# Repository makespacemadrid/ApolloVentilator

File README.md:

# ApolloVentilator

Information: Checkout our [wiki](https://github.com/makespacemadrid/ApolloVentilator/wiki)

### Schematic

### Prototype 1 @ MakeSpace Madrid

### Prototype 2 @ Miguel's Workshop

## Getting started

### Linux

```
$ apt-get install libcairo2-dev libgirepository1.0-dev python3-cairo-dev
```

### Mac

```
$ brew install pygobject3 gtk+3 libnotify
```

### App (Python 3)

From ```./gui```

Install system dependencies (Debian-based):

```
$ pip install -r requirements.txt
$ ./main.py
```

## Requirements:
2 ventilators mode
* Pressure Regulated Volume Controlled (PCV): set pressure delivered during period of inspiration. The voume measured is shown as data on display. 
* Volume Regulated Pressure controlled (VCV): The tidal volume is set and it adapts the pressure to the lowest. Here the important data are: tidal volume, upper alarm and lower current volume. Useful parameters: tidal volume, respiratory rate. There is a limit pressure and during inspiration period.

If patient stops breathing, there is a failsafe that set to mandatory breathing when it's detected.

During inspiration:

* Inspiration pressure: The plateau pressure is adjusted to volume hard limit (32 cmH2O by default, and could increate to 70cmH2O)
* Peak pressure: 2cmH2O greater than plateau.
* VCV pressure limit (15-40cm2 with increments of 5)
* Failsafe valve that opens always at 80cmH20 (or lower)

* PEEP: 5-10 with increments of 5. The circuit must be pressured.
* IE ratio: 1:1, 1:2, 1:3
* Respiratory rate: 10-30 bpm with increments of 2.
* Tidal volume: 40ml +-10, 350 +-50, 250-600 +-50,up to 8000. 
* Weight body and volume calculated based on 6ml/kg.

## Alarms

* Gas failure
* Electricity failure
* Machine switched off
* Inspiration pressure exceeded
* Inspiration pressure not achieved
* PEEP pressure not achieved
* Tidal volume not achieved
* Tidal volume exceeded
* Resistance: peak pressure - plateau pressure > 2cmH2O
* Compliance
* Volume Leakage

## Monitoring
### Settings
* Tidal volume
* Frequency
* PEEP
* FI02
* Ventilation Mode

### Current status
* Tidal volume
* Breathing rate
* PEEP
* Plateau pressure
* FI02

The normal healthy O2 consuption is 250mL/min, and could be increased until, for example 500 mL/min in a sepsis.

### Parallel measures 

* Presión arteria
* Frecuencia cardiaca
* ECG
* Nivel de sedación
* Posicion del tubo e inflado del neumotaponamiento
* Intercambio gaseoso (pulsiometria SO2), capnografía y gasometrías arteriales periodicas para obtener los **índices de oxigenación** (clave para evaluar la desintubación del paciente).

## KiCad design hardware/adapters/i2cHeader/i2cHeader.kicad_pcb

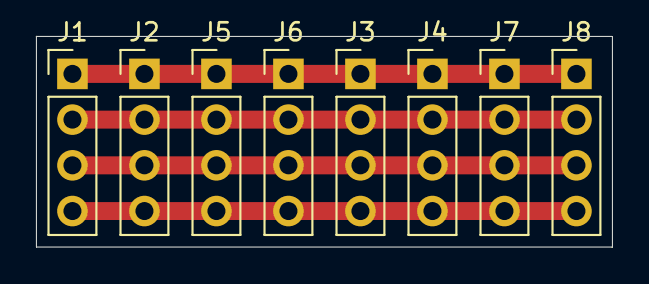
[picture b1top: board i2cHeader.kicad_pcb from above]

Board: 2 copper layers, 32.0 x 11.7 mm, 8 parts (0 on the bottom side), 4 nets.

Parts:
J1, J2, J3, J4, J5, J6, J7, J8: Conn_01x04; PinHeader_1x04_P2.54mm_Vertical

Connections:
DATA: J1.3, J2.3, J3.3, J4.3, J5.3, J6.3, J7.3, J8.3
GND: J1.4, J2.4, J3.4, J4.4, J5.4, J6.4, J7.4, J8.4
SCK: J1.2, J2.2, J3.2, J4.2, J5.2, J6.2, J7.2, J8.2
VDD: J1.1, J2.1, J3.1, J4.1, J5.1, J6.1, J7.1, J8.1

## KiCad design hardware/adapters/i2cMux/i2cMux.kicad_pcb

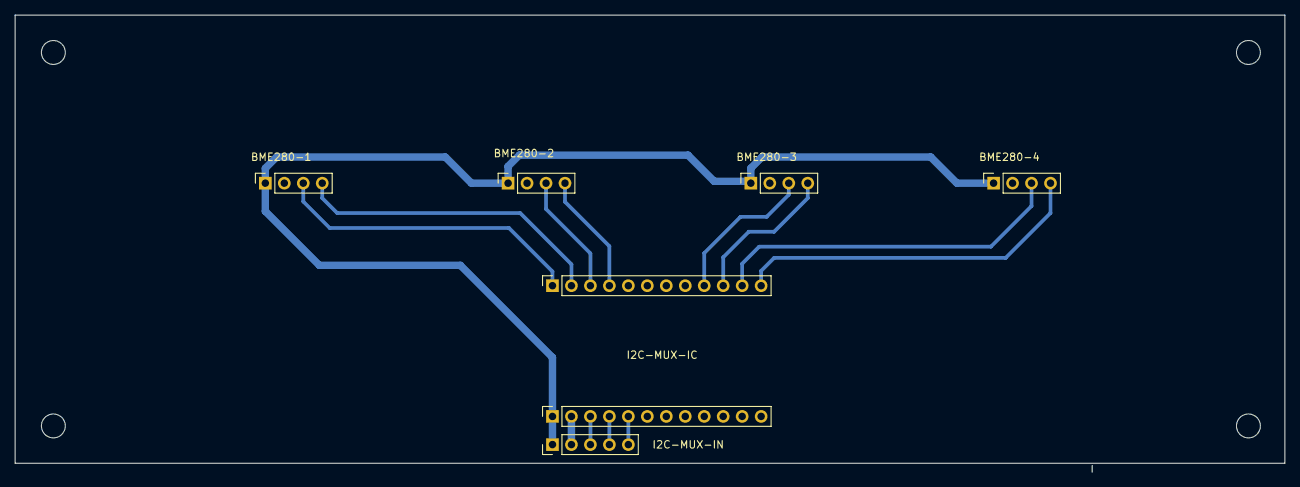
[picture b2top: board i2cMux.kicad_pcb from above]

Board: 2 copper layers, 170.0 x 61.2 mm, 7 parts (0 on the bottom side), 13 nets.

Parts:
BME280-1: BME280-1; PinSocket_1x04_P2.54mm_Vertical
BME280-2: BME280-2; PinSocket_1x04_P2.54mm_Vertical
BME280-3: BME280-3; PinSocket_1x04_P2.54mm_Vertical
BME280-4: BME280-4; PinSocket_1x04_P2.54mm_Vertical
I2C-MUX-IC: I2C-MUX; PinSocket_1x12_P2.54mm_Vertical
I2C-MUX-IN: Conn_01x05; PinHeader_1x05_P2.54mm_Vertical
J2: I2C-MUX; PinSocket_1x12_P2.54mm_Vertical

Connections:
/RST: I2C-MUX-IC.5, I2C-MUX-IN.5
/SCL: I2C-MUX-IC.4, I2C-MUX-IN.4
/SDA: I2C-MUX-IC.3, I2C-MUX-IN.3
GND: BME280-1.2, BME280-2.2, BME280-3.2, BME280-4.2, I2C-MUX-IC.2, I2C-MUX-IN.2
SC2: BME280-4.3, J2.11
SC3: BME280-3.3, J2.9
SC6: BME280-2.3, J2.3
SC7: BME280-1.3, J2.1
SD2: BME280-4.4, J2.12
SD3: BME280-3.4, J2.10
SD6: BME280-2.4, J2.4
SD7: BME280-1.4, J2.2
VIN: BME280-1.1, BME280-2.1, BME280-3.1, BME280-4.1, I2C-MUX-IC.1, I2C-MUX-IN.1

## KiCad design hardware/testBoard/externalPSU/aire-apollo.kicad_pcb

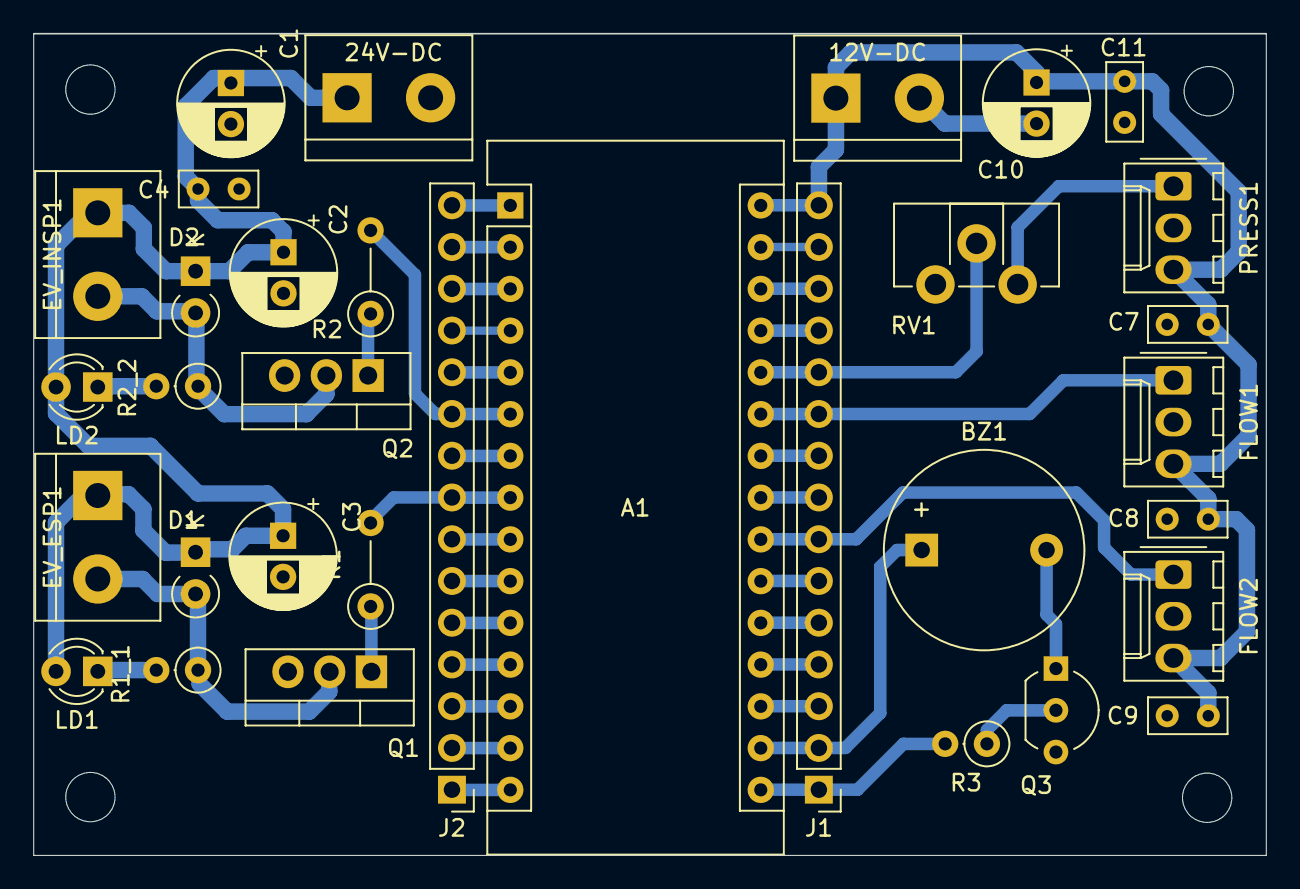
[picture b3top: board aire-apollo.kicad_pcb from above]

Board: 2 copper layers, 75.0 x 50.0 mm, 33 parts (0 on the bottom side), 38 nets.

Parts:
12V-DC, 24V-DC: CON; TerminalBlock_bornier-2_P5.08mm
A1: Arduino_Nano_v3.x; Arduino_Nano
BZ1: Buzzer; Buzzer_12x9.5RM7.6
C1, C2, C3: 33uf/63V; CP_Radial_D6.3mm_P2.50mm
C4, C7, C8, C9, C11: 100nF; C_Rect_L4.6mm_W2.0mm_P2.50mm_MKS02_FKP02
C10: 100uf/16V; CP_Radial_D6.3mm_P2.50mm
D1, D2: 1N4007; D_A-405_P2.54mm_Vertical_KathodeUp
EV_ESP1: CON3; TerminalBlock_bornier-2_P5.08mm
EV_INSP1: CON2; TerminalBlock_bornier-2_P5.08mm
FLOW1: CON5; Molex_KK-254_AE-6410-03A_1x03_P2.54mm_Vertical
FLOW2: CON6; Molex_KK-254_AE-6410-03A_1x03_P2.54mm_Vertical
J1, J2: Conn_01x15; PinHeader_1x15_P2.54mm_Vertical
LD1, LD2: LED; LED_D3.0mm
PRESS1: CON4; Molex_KK-254_AE-6410-03A_1x03_P2.54mm_Vertical
Q1, Q2: TIP121; TO-220-3_Vertical
Q3: BC548; TO-92_Inline_Wide
R1, R2: 1K; R_Axial_DIN0207_L6.3mm_D2.5mm_P5.08mm_Vertical
R1_1, R2_2: 1k2; R_Axial_DIN0207_L6.3mm_D2.5mm_P2.54mm_Vertical
R3: 1K; R_Axial_DIN0207_L6.3mm_D2.5mm_P2.54mm_Vertical
RV1: 10K; Potentiometer_ACP_CA9-H2,5_Horizontal

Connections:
+12V: 12V-DC.1, A1.30, C7.1, C8.1, C9.1, C10.1, C11.1, FLOW1.3, FLOW2.3, J1.15, PRESS1.3
+24V: 24V-DC.1, C1.1, C2.1, C3.1, C4.1, D1.1, D2.1, EV_ESP1.1, EV_INSP1.1, LD1.2, LD2.2
/3V3: A1.17, BZ1.1, J1.2
/+5V: A1.27, J1.12
/A0: A1.19, J1.4
/A1: A1.20, J1.5
/A2: A1.21, J1.6
/A4: A1.23, J1.8
/A5: A1.24, J1.9
/AREF: A1.18, J1.3
/D0: A1.2, J2.14
/D1: A1.1, J2.15
/D2: A1.5, J2.11
/D4: A1.7, J2.9
/D6: A1.9, J2.7
/D7: A1.10, J2.6
/D8: A1.11, J2.5
/D9: A1.12, J2.4
/D10: A1.13, J2.3
/D11: A1.14, J2.2
/D12: A1.15, J2.1
/D13: A1.16, J1.1, R3.2
/RST: A1.3, A1.28, J1.13, J2.13
A3: A1.22, FLOW2.1, J1.7
A6: A1.25, FLOW1.1, J1.10
A7: A1.26, J1.11, RV1.2
D3: A1.6, J2.10, R2.2
D5: A1.8, J2.8, R1.2
GND: 12V-DC.2, 24V-DC.2, A1.4, A1.29, C1.2, C2.2, C3.2, C4.2, C7.2, C8.2, C9.2, C10.2, C11.2, FLOW1.2, FLOW2.2, J1.14, J2.12, PRESS1.2, Q1.3, Q2.3, Q3.3, RV1.1
unnamed: BZ1.2, Q3.1
unnamed: D1.2, EV_ESP1.2, Q1.2, R1_1.1
unnamed: D2.2, EV_INSP1.2, Q2.2, R2_2.1
unnamed: LD1.1, R1_1.2
unnamed: LD2.1, R2_2.2
unnamed: PRESS1.1, RV1.3
unnamed: Q1.1, R1.1
unnamed: Q2.1, R2.1
unnamed: Q3.2, R3.1

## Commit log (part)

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2020-03-20 Commit inicial
    Añadido firmware de pruebas del primer dia. No hay gran cosa, medir la presion y si baja activar la electrovalvula.
2020-03-20 añadido diagrama de flujo de funcionamiento de un respirador
2020-03-20 basic functional pseudocode
2020-03-21 metrics pressure and volume
2020-03-22 realtime update data point by point
2020-03-22 cli with random data option and serial port reading, requirements updated
2020-03-22 print number of values parametrized
2020-03-22 syntax error defining type str fix
2020-03-22 Integración de pseudocodigo y configuración sensor presión
2020-03-22 Update gitignore
2020-03-22 Added getMetricVolumeExit()
2020-03-22 Mostrar GUI con gráficas de ejemplo
    Goal
    - Ejecutar una interfaz gráfica que permita visualizar gráficos con matplotlib
    Done
    - Test from_file proof of concept
    - Show subplots in apollo proof of concept
    - Write Layout using glade
2020-03-22 duplicate script
2020-03-22 Added Log to GUI
2020-03-22 .gitignore pycache
2020-03-23 refactor updating data with random values inside gtk app
2020-03-23 notify example, gamma distribution function test
2020-03-23 Refactor, bug-hunting y primeras pruebas :)
2020-03-23 Update .gitignore for vscode
2020-03-23 Mostrar GUI con gráficas de ejemplo
    Goal
    - Ejecutar una interfaz gráfica que permita visualizar gráficos con matplotlib
    Done
    - Test from_file proof of concept
    - Show subplots in apollo proof of concept
    - Write Layout using glade
2020-03-23 Añade prefijo a la salida para separar DEBUG, DATA
2020-03-23 Añadido prefijo de alarma
2020-03-24 Added ApolloBME subclass
2020-03-24 - Add TODOs and Finish Flow
2020-03-24 - Add TODOs and Finish Flow more
2020-03-24 - organize comments
2020-03-25 README gui requirements
2020-03-25 wiki link for general project information
2020-03-25 set dependencies into a requirements file
2020-03-25 Added MKSM subclases
2020-03-25 Add Comunications
    - Move data function
    - Generate Alert function
2020-03-25 new parameters in device
2020-03-25 Fix comminucations
2020-03-26 Harware test board
2020-03-26 Innitial MechVentilation
2020-03-26 better window fit
2020-03-26 requirements documentation
2020-03-26 serial port data reception
2020-03-26 Clean glued main and hal
2020-03-26 Update to work with basic leds
2020-03-26 alert parser reading from serial port
2020-03-26 Mejoras MechVentilation
2020-03-26 data command parser
2020-03-26 Protocol gtk (#20)
    Goal
    - Parse and handle serial port commands and data
    Done
    - alert parser reading from serial port
    - data command parser
2020-03-26 [sw] Add Send Configuration Command and Manage Debug Messages
    Goal
    - Send configuration command to the device via serial port
    - Manage debug messages from the device
    Tasks
    - Add *DEBUG* case
    - Add send_command_action
2020-03-26 - Checkeando error windows size
2020-03-27 mac requirements, logging, debug and config schema proposal
2020-03-27 Add manual control system
2020-03-27 añadida dependencia python3-cairo-dev
2020-03-27 Fix window resize better gtk layout (#26)
    * Fix for window resizing and better layout of Device window
    In this commit, we have removed the font setting, 40 points is
    a REALLY big font and made all controls gigantic. Removing that
    setting (you should really let the desktop theme decide) made
    it work as expected.
    Also, I took the liberty of creating a better layout for the controls
2020-03-27 remove unnecessary device1, fix data plot
2020-03-28 Aglomeracion y refactor
2020-03-28 Bug hunting!
    2 horas por entry != enryt
2020-03-28 GUI research
2020-03-28 Added new Honeywell TruStability SPI pressure sensor
2020-03-28 Added .vscode to gitignore
2020-03-28 some GUI screenshots
2020-03-28 integración completa
    -puede que quede algun bug
    -Todavia queda por limpiar y ordenar.... to be continued
2020-03-28 añadida libreria mstimer2
2020-03-28 fix filter data
2020-03-28 no sleeps
2020-03-28 default serial port
2020-03-28 Add ApolloConfiguration
2020-03-28 Added member prefix
2020-03-29 print faster
2020-03-29 Test Ci CD
2020-03-29 Add workflow to github
2020-03-29 Fix path
2020-03-29 Fix path and configure
2020-03-29 plot fix?
2020-03-29 new screenshots
2020-03-29 Limpieza
2020-03-29 Mas datos
2020-03-29 Set Zero in pression for sensor BME280
2020-03-29 gui chart with pyqtchart
2020-03-29 requirements
2020-03-29 diseño de valvula de pinza imprimible(testing)
2020-03-29 Fix errors in merge configuration
2020-03-29 Fix configuration module integration
2020-03-30 js websocket chart test
2020-03-30 Fix bug in MechVentilation
2020-03-30 Fix error in Ventilator and alert in hight pressure.
2020-03-30 Update Ventilator
2020-03-30 fix para poder hacer pruebas
2020-03-30 chart wrong values
2020-03-30 chart size
2020-03-31 gui: Fix a condition
    ("DATA" or "ALERT" or "DEBUG" or "CONFIG") evaluates to "DATA", redo
    this condition to handle the four commands.
2020-03-31 gui: Read serial data in the main thread
    Drop the extra thread for serial reading. Writing will still block
    (briefly)..
2020-03-31 Add feature Alarms
2020-04-01 Create LICENSE
2020-04-02 some pocs
2020-04-02 Issue: Añadir información de documentación en README Authors: - @o-hgm
    Objetivo
    Algutinar en README la información sobre:
    - Colaboración
    - Licencia
    - Listado de material
    - Funcionamiento del software, firmware
2020-04-02 Issue: Portar GUI a QT
    Autor/a:
    - @maesbrisa
    - @o-hgm
    Descripción
    - Dado que existen problemas en el repintado de gráficas usando GTK+ se ha decidido portar a QT, que presenta facilidades para el uso de gráficas con datos en tiempo real
    Objetivo
2020-04-02 Set theme jekyll-theme-minimal
2020-04-02 Set theme jekyll-theme-dinky
2020-04-02 Set theme jekyll-theme-slate
2020-04-02 Set theme jekyll-theme-cayman
2020-04-03 Refactor and renaming MechVentilator
2020-04-03 reorder paths
2020-04-03 duplicated gui path inside software
2020-04-04 Removed pointers
2020-04-04 Updated libraries
2020-04-04 WIP: Integration of PID
2020-04-04 two plots graphs
2020-04-05 recover double plot
2020-04-05 Renaming
2020-04-05 Add style gide
2020-04-05 limpieza de las funciones de hal que usaban los punteros a sensor y creación de los metodos necesarios para acceder a esas funciones.
2020-04-05 añadido fichero para overrides de configuracion
2020-04-05 better data lectures, excepts during data processing
2020-04-05 fix status valve
2020-04-05 Reorder files and name class
2020-04-05 fix double
2020-04-05 Created new BME differencial sensor
2020-04-06 wip, ajuste de los PIDs
2020-04-06 Valves Works
2020-04-07 Add Valve in stepper
2020-04-08 wip - pruebas con otra libreria pid
2020-04-08 Add calibrate and offsets
2020-04-08 Add new mode and configuration to pause and resume the machine
2020-04-08 Add new library to analog pressure sensor
    It's important that the sensor are linear!!!!
2020-04-08 wip - integration
2020-04-09 wip - ahora se mueve en ambas direcciones
2020-04-09 Fix errors in params
2020-04-09 fix renaming
2020-04-09 Cada cosa a su carpeta
2020-04-09 modificado: Firmware/aire_apollo/src/Valve/StepperNema.h
2020-04-09 Feaure/integration pid (#66)
    * WIP: Integration of PID
    * WIP: Integration of PID
    * Renaming
    * limpieza de las funciones de hal que usaban los punteros a sensor y creación de los metodos necesarios para acceder a esas funciones.
    * añadido fichero para overrides de configuracion
    * fix status valve
2020-04-09 New Sfm3000FlowSensor
2020-04-10 WIP: cazafantasmas
2020-04-10 bug hunting
2020-04-10 Fix merge
2020-04-10 add gitignore
2020-04-10 sync work in progress
2020-04-10 Add Dummy sensor
2020-04-10 Update and reconfigure NemaValvle
2020-04-11 classes,buffer, timers
2020-04-11 stepperNema ng, changelog: -Añadida secuencia de home y test inicial.
    Despues de hacer home se va a la posicion maxima y se cuentan los pasos de vuelta. si el mecanismo y el motor están ok, sera el mismo numero de ida que de vuelta.
    -Revision del tema de velocidad:
    Para poder superar cierta velocidad en el stepper en modo asincrono hay que disponer un sistema de interrupiones mas rápido/sofisticado. Pruebas iniciales, se deja en modo sincrono para pruebas.
    -Hay un bug en la posicion inicial, va a home, de ahi a posicion de inicio y en el primer movimiento vuelve a aplicar el offset de inicio.
    -Pensamiento... La valvula de pinza cierra al avanzar mientras que la valvula de submarinismo
2020-04-11 fixes and debugging messages
2020-04-12 mqtt-grafana script
2020-04-14 añadida libreria StepperDriver
2020-04-14 New Software I2C sensor
2020-04-14 volviendome loco un rato
2020-04-14 Moved declaration to .cpp
2020-04-16 -Soporte valvula Nema -Soporte Sensirion -Pruebas y bug-hunting
2020-04-16 Añadida opcion para activar los pullup en los finales de carrera listo para mergue!
2020-04-16 añadido TODO con tareas pendientes a la clase stepperNema
2020-04-17 Working Extenral display
2020-04-17 mqtt volume data param
2020-04-17 mqtt new params
2020-04-18 wrong index
2020-04-18 -Testing del sensor del sensor de flujo sensirion -Hackeo del sensor softSfm para que funcione(el softwire lee bien los datos pero no los offset/scale) -Mejoras en la clase de valvula. ahora hay un s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
2020-04-21 socketio requirements
2020-04-24 Parece que funciona
2020-04-24 Otro concepto de valvula de pinza
2020-04-24 refactor-rename
2020-05-02 Iteracion de la valvula de pinza Conectores varios
2020-05-02 añadidas imagenes a la portada del repo
2020-05-02 fix images
2020-05-02 fix image 2
2020-05-02 Soporte para esp32 Trabajos varios en las clases y en el hal
2020-05-05 schema to start
2020-05-05 plot update
2020-05-05 initialized without shit data, counter as time, simplified update list when max length is achieved
2020-05-06 Sistema de calibracion de la rampa de presion - Proof of concept
2020-05-09 añadido fichero strings.h
2020-05-10 Protocolo de comunicacion por JSON Aumentada la velocidad del serie a 921600
    Tiempo de trasmision:
    115200: 9msec
    250000: 4msec
    921600: 1msec
2020-05-11 añadida libreria autotune pid.
    La libreria original da errores de compilacion en el esp. Le he cambiado las variables min max para arreglarlo
2020-05-11 wip - actualizacion
2020-05-11 json data
2020-05-11 fix merge conflicts
2020-05-12 debug messages
2020-05-12 baudrate
2020-05-12 Fix steppernema nuevo env para el tercer prototipo
2020-05-14 mqtt sub-topics. Mqtt subscribe client.
2020-05-15 Extra script to ejecute js monitor after upload
2020-05-15 Added I2C multiplexer to diff sensor
2020-05-15 Added Venturi flow sensor
2020-05-16 Inicializa correctamente nextActionTime
2020-05-16 Revert "Inicializa correctamente nextActionTime"
    This reverts commit c9988e1db73af1b46285becc860b9d22e3d7d45f.
2020-05-16 Revert "Revert "Inicializa correctamente nextActionTime""
    This reverts commit c8677b241fb9993a0618d233f5b58667d6bb4b38.
2020-05-16 auto calibracion del pid que gestiona la presion constante
2020-05-16 fix al sistema de sobre presion
2020-05-16 ajustes
2020-05-17 fix compiler warning
2020-05-19 Selecciona correctamente el bus i2c
2020-05-19 prueba de pid 3
2020-05-19 ignorar carpeta node_modules
2020-05-19 ignore
2020-05-19 ajuste
2020-05-19 test5
2020-05-22 Trabajos varios
    -Añadidos parametros en el defaults para todas las variables del stepper
    -ajustes a la libreria de autopid
    -ajustes al proceso de autocalibrado del pid
    -escuchar en el serie
    -implementado json command
    -implementado json hwStatus
2020-05-22 añadido script para abrir automaticamente el node
2020-05-22 fix portspeed
2020-05-22 gitignore package-lock.json
2020-05-22 fixes
2020-05-22 add env
2020-05-29 let there be math! -mecanismo de frenada de presion, prueba de concepto
2020-06-03 Nueva clase apollostorage reorganizacion de ficheros
2020-06-03 pof2
2020-06-03 menos prints
2020-06-14 -configuracion y calibracion. -nueva interfaz pid -nueva clase de ventilador
2020-06-21 -Reorganizacion de las clases -Nueva clase protocolo -nuevo fichero globalfunctions con funciones globales para la gestions de contadores -nuevo sistema de calibracion
    mucho de todo y todavia falta
2020-11-03 Cambio en nombre de método para igualarlo a superclase
2021-02-11 First upload
2021-02-11 Included Nextion screen in the repository
2021-02-11 Repository changes
2021-02-11 Cambios en la frecuencia de actualiación de datos para probar la pantalla
